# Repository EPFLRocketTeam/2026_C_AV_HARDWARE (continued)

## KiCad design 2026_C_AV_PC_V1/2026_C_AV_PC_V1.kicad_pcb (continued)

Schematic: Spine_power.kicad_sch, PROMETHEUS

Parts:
C5: 1u; C_0603_1608Metric
C6: 4u7; C_0603_1608Metric
C7: 1000p; C_0603_1608Metric
C8, C9, C11, C28, C29, C30, C50: 0u1; C_0603_1608Metric
C10: 100n; C_0603_1608Metric
C33, C34: 10u; C_0603_1608Metric
D9, D29, D53, D54, D55: PESD5V0S1UL; D_SOD-882; Mouser PESD5V0S1UL-QYL
D11, D12, D25, D36: LED; LED_0603_1608Metric
D57, D58, D61, D62, D63, D64: PESD3V3S1UL; D_SOD-882; Mouser 771-PESD3V3L1UL315
F1: Polyfuse; D_0805_2012Metric
F2: Polyfuse; Fuse_2920_7451Metric
H1, H2, H3, H4: MountingHole_Pad; MountingHole_2.2mm_M2_Pad
IC1: INA228AIDGSR; INA228; Mouser Part Number 595-INA228AIDGSR
IC4: MCP1642D-50I_MS; MCP1642; Mouser Part Number 579-MCP1642D-50I/MS
IC9: TPS25221DRVR; SON65P200X200X80-7N; Mouser Part Number 595-TPS25221DRVR
J7, J19: USB_B_Mini; USB_Mini-B_Lumberg_2486_01_Horizontal
J8: 24Vin; AMASS_XT60-M; PARTREV V1.2
J9: SPINE_in; STEWART_SS-12800-009; PARTREV A0; DigiKey_Part_Number 380-SS-12800-009-ND
J10: microSD_holder; Mouser Part Number 798-DM3ATSFPEJM541
J15: SPINE_out; STEWART_SS-12800-009; PARTREV A0; DigiKey_Part_Number 380-SS-12800-009-ND
J22: 24Vout; AMASS_XT60-M; PARTREV V1.2
JP3, JP4: SolderJumper_2_Open; SolderJumper-2_P1.3mm_Open_RoundedPad1.0x1.5mm
L1: 4u7; WE-TPC_282892; Mouser Part Number 710-744025004
R13: 100k; R_0603_1608Metric
R14: 13m; R_0805_2012Metric
R15: 120; R_0603_1608Metric
R16, R17, R35, R45: 1k1; R_0603_1608Metric
R32: 4K7; R_0603_1608Metric
R33: 32k; R_0603_1608Metric
R34, R60: 10k; R_0603_1608Metric
R58, R59: 54k9; R_0603_1608Metric
TP5: +24V; TestPoint_THTPad_D1.5mm_Drill0.7mm
TP6: CANH; TestPoint_THTPad_D1.5mm_Drill0.7mm
TP7: CANL; TestPoint_THTPad_D1.5mm_Drill0.7mm
TP8: +5V; TestPoint_THTPad_D1.5mm_Drill0.7mm
TP9: +3V3; TestPoint_THTPad_D1.5mm_Drill0.7mm
TP11: 5V_IN_SPINE; TestPoint_THTPad_D1.5mm_Drill0.7mm
TP13: 5V_IN_USB; TestPoint_THTPad_D1.5mm_Drill0.7mm
TP16: +5V_IN; TestPoint_THTPad_D1.5mm_Drill0.7mm
U5: MCP1727-3302xSN; SOIC-8_3.9x4.9mm_P1.27mm
U6: MCP2542FDxMF; SOIC-8_3.9x4.9mm_P1.27mm
U10: TPS2116DRL; SOT-583-8
U12, U13: USBLC6-2P6; SOT-666

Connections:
+3V3: C5.1, C8.2, C10.2, C11.2, D12.2 (A), IC1.1 (A1), IC1.2 (A0), IC1.6 (VS), J10.4 (VDD), R13.1, TP9.1, U5.7 (Sense), U5.8 (Vout), U6.5 (VIO); also elsewhere on the board
+5V: C9.1, C34.2, D11.2 (A), IC4.4 (VOUT), TP8.1, U6.3 (VDD); also elsewhere on the board
+24V: D36.2 (A), IC1.9 (IN-), R14.2, TP5.1; also elsewhere on the board
/Project Architecture/STM32/FDCAN_RX: U6.4 (RXD); also elsewhere on the board
/Project Architecture/STM32/FDCAN_TX: U6.1 (TXD); also elsewhere on the board
/Project Architecture/STM32/PWRGD: R13.2, U5.5 (PWRGD); also elsewhere on the board
/Project Architecture/STM32/SCL: IC1.4 (SDA); also elsewhere on the board
/Project Architecture/STM32/SDA: IC1.5 (SCL); also elsewhere on the board
/Project Architecture/STM32/SD_CLK: D64.1 (K), J10.5 (CLK); also elsewhere on the board
/Project Architecture/STM32/SD_CMD: D63.1 (K), J10.3 (CMD); also elsewhere on the board
/Project Architecture/STM32/SD_DAT0: D58.1 (K), J10.7 (DAT0); also elsewhere on the board
/Project Architecture/STM32/SD_DAT1: D61.1 (K), J10.8 (DAT1); also elsewhere on the board
/Project Architecture/STM32/SD_DAT2: D57.1 (K), J10.1 (DAT2); also elsewhere on the board
/Project Architecture/STM32/SD_DAT3: D62.1 (K), J10.2 (CD/DAT3); also elsewhere on the board
/Project Architecture/STM32/USB2_D+: U13.1 (I/O1); also elsewhere on the board
/Project Architecture/STM32/USB2_D-: U13.3 (I/O2); also elsewhere on the board
/Project Architecture/STM32/USB_D+: U12.1 (I/O1); also elsewhere on the board
/Project Architecture/STM32/USB_D-: U12.3 (I/O2); also elsewhere on the board
/Project Architecture/Spine&power/3V3_K: D12.1 (K), R17.1
/Project Architecture/Spine&power/5V_K: D11.1 (K), R16.1
/Project Architecture/Spine&power/24V_K: D36.1 (K), R45.1
/Project Architecture/Spine&power/24V_c: F2.1, J8.P (POS), J22.P (POS)
/Project Architecture/Spine&power/+5V_IN: C6.1, C30.2, C33.1, IC4.8 (VIN), JP3.1 (A), L1.1, R32.1, TP16.1, U5.1 (Vin), U5.2 (Vin), U5.3 (~SHDN), U10.2 (VOUT), U10.7 (VOUT)
/Project Architecture/Spine&power/+5V_SPINE: C28.2, D9.1 (K), J9.4, J15.4, R33.1, TP11.1, U10.3 (VIN1), U10.5 (MODE)
/Project Architecture/Spine&power/+5V_USB: C50.2, IC9.4 (EN), IC9.6 (IN), J7.1 (VBUS), R59.1, TP13.1, U12.5 (VBUS)
/Project Architecture/Spine&power/+5V_USB_p: F1.1, IC9.1 (OUT)
/Project Architecture/Spine&power/CANH: D29.1 (K), D54.1 (K), J9.2, J15.2, R15.1, TP6.1, U6.7 (CANH)
/Project Architecture/Spine&power/CANL: D53.1 (K), D55.1 (K), J9.3, J15.3, R15.2, TP7.1, U6.6 (CANL)
/Project Architecture/Spine&power/D2+: J19.3 (D+), U13.6 (I/O1)
/Project Architecture/Spine&power/D2-: J19.2 (D-), U13.4 (I/O2)
/Project Architecture/Spine&power/D+: J7.3 (D+), U12.6 (I/O1)
/Project Architecture/Spine&power/D-: J7.2 (D-), U12.4 (I/O2)
/Project Architecture/Spine&power/Delay: C7.1, U5.6 (Cdelay)
/Project Architecture/Spine&power/EN: IC4.1 (EN), JP3.2 (B), JP4.2 (B)
/Project Architecture/Spine&power/PR1: R33.2, R34.1, U10.4 (PR1)
/Project Architecture/Spine&power/ST: D25.2 (A), JP4.1 (A), R32.2, R60.1, U10.8 (ST)
/Project Architecture/Spine&power/ST_K: D25.1 (K), R35.1
/Project Architecture/Spine&power/SW: IC4.5 (SW), L1.2
/Project Architecture/Spine&power/VIN2: C29.2, F1.2, U10.6 (VIN2)
/Project Architecture/Spine&power/Vin+: F2.2, IC1.8 (VBUS), IC1.10 (IN+), R14.1
GND: C5.2, C6.2, C7.2, C8.1, C9.2, C10.1, C11.1, C28.1, C29.1, C30.1, C33.2, C34.1, C50.1, D9.2 (A), D29.2 (A), D53.2 (A), D54.2 (A), D55.2 (A), D57.2 (A), D58.2 (A), D61.2 (A), D62.2 (A), D63.2 (A), D64.2 (A), H1.1, H2.1, H3.1, H4.1, IC1.7 (GND), IC4.6 (PGND), IC4.7 (SGND), IC9.5 (GND), IC9.7 (EP), J7.5 (GND), J7.6 (Shield), J8.N (NEG), J9.1, J9.SH1 (SHIELD), J9.SH2 (SHIELD), J10.6 (VSS), J10.MP1, J10.MP2, J10.MP3, J10.MP4, J10.MP5, J10.MP6, J10.MP7, J15.1, J15.SH1 (SHIELD), J15.SH2 (SHIELD), J19.5 (GND), J19.6 (Shield), J22.N (NEG), R16.2, R17.2, R34.2, R35.2, R45.2, R58.2, R60.2, U5.4 (GND), U6.2 (VSS), U6.8 (STBY), U6.9 (VSS), U10.1 (GND), U12.2 (GND), U13.2 (GND); also elsewhere on the board
unnamed: IC9.2 (ILIM), R58.1
unnamed: IC9.3 (~FAULT), R59.2

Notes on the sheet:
SPINE & POWER
I2C Address: 0x45
Status LED + Debug
5V Boost
Power MUX
Tension sensor
+3V3 LDO
CAN FD Transceiver
SPINE connector
Over Current Protection USB
DESIGN NOTES: Internal ESD protection +13kV
MicroSD holder
ST from the power mux desable the boost when USB is connected to prevent back current
USB for data + power
Battery power

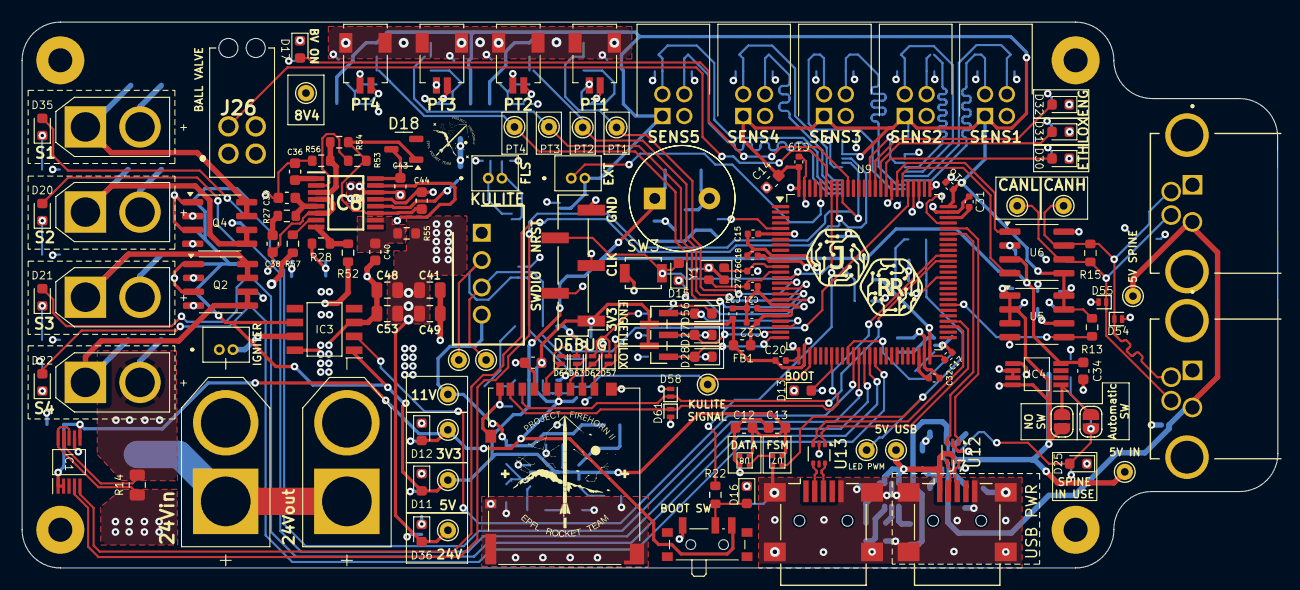
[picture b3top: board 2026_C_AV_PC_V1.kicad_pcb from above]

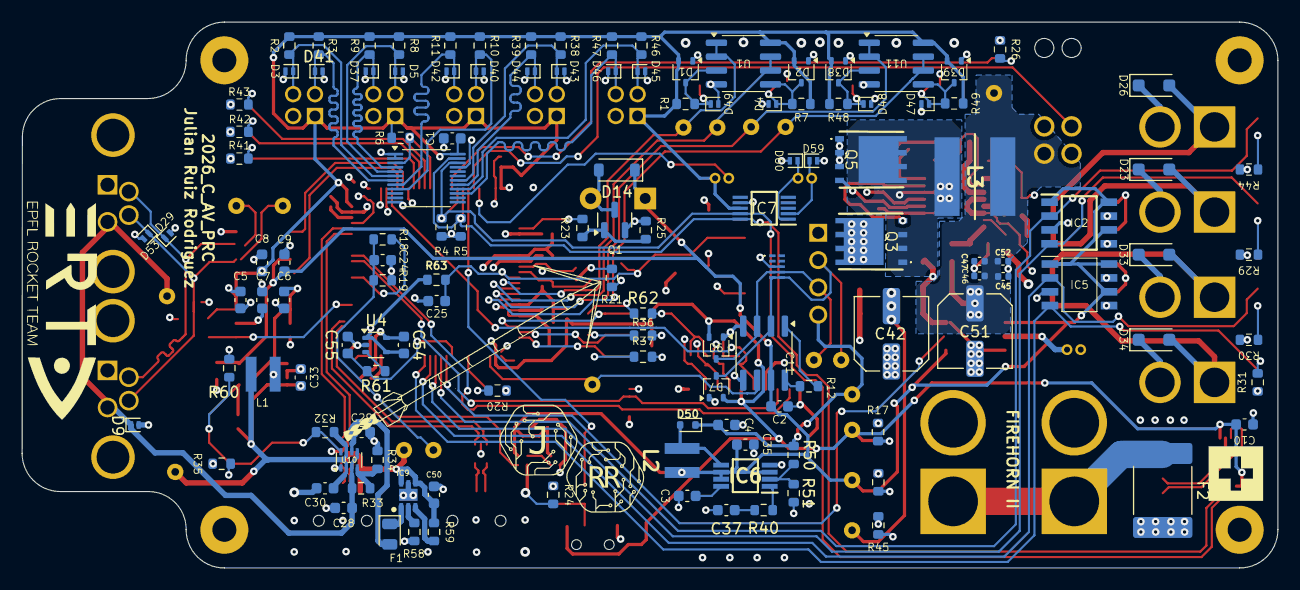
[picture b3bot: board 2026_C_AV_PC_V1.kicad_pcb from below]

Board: 4 copper layers, 115.0 x 50.0 mm, 265 parts (129 on the bottom side), 145 nets.

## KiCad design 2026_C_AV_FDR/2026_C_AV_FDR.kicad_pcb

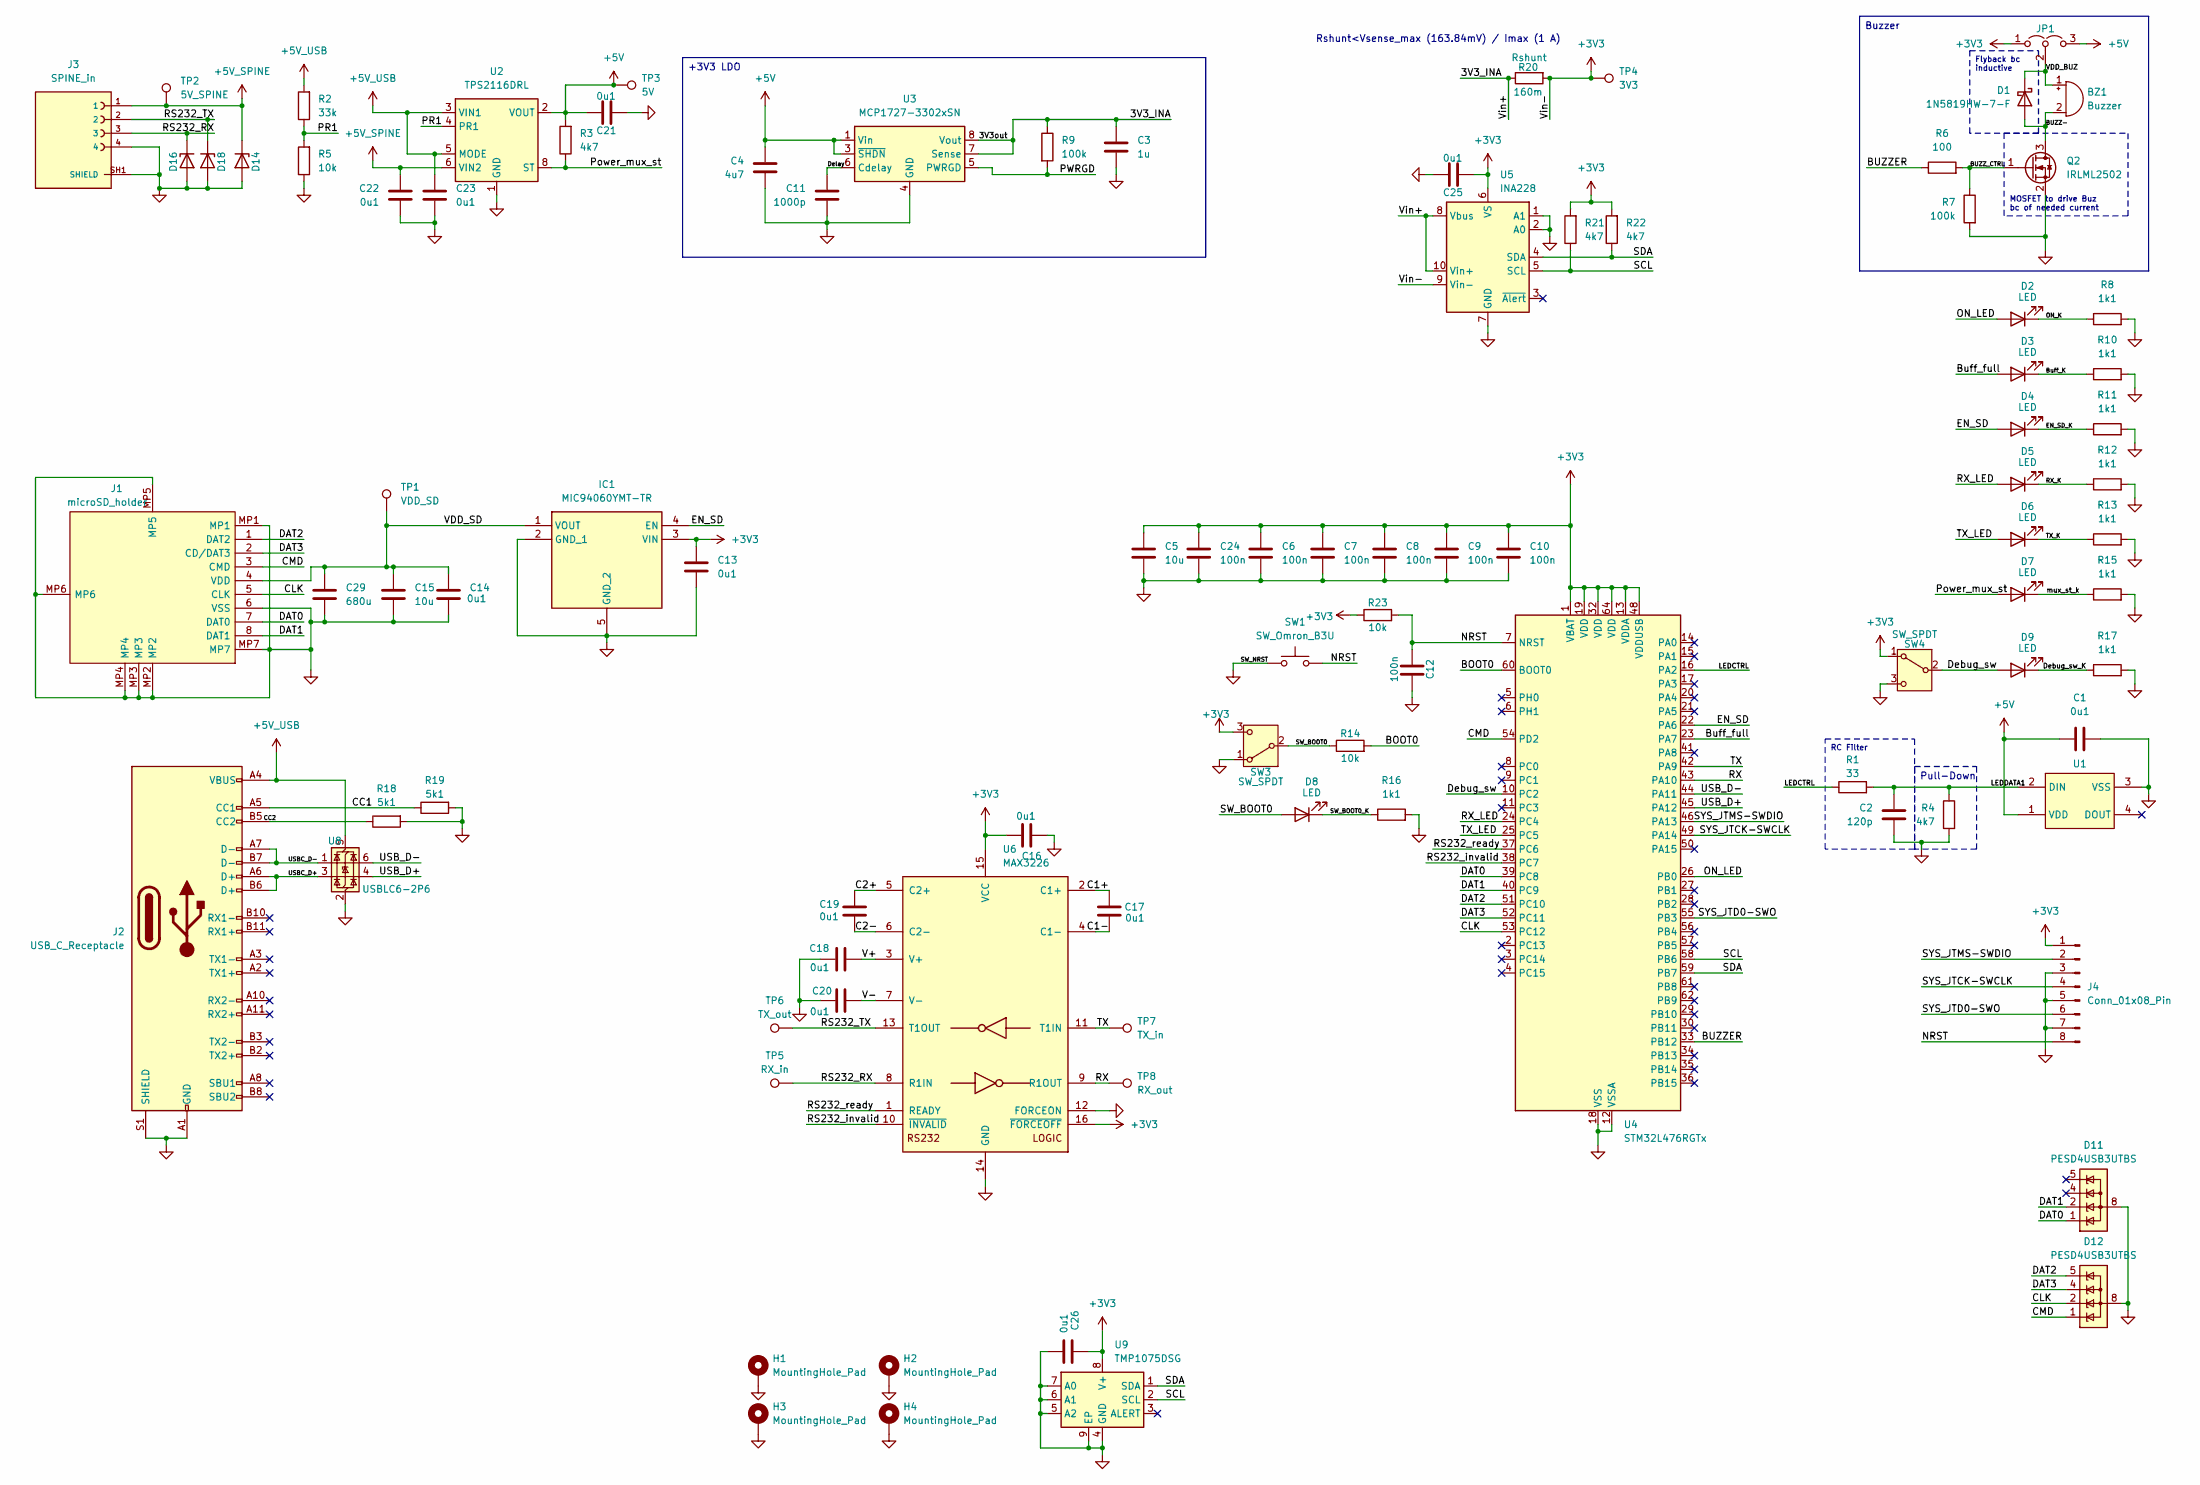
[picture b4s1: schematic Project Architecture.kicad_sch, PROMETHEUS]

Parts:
BZ1: Buzzer
C1, C13, C14, C16, C17, C18, C19, C20, C21, C22, C23, C25, C26: 0u1; C_0603_1608Metric
C2: 120p; C_0603_1608Metric
C3: 1u; C_0603_1608Metric
C4: 4u7; C_0603_1608Metric
C5, C15: 10u; C_0603_1608Metric
C6, C7, C8, C9, C10, C24: 100n; C_0402_1005Metric
C11: 1000p; C_0603_1608Metric
C12: 100n; C_0603_1608Metric
C29: 680u; C_Elec_6.3x7.7; Mouser No 667-EEE-FTJ681XAP
D1: 1N5819HW-7-F; D_SOD-123
D2, D3, D4, D5, D6, D7, D8, D9: LED; LED_0603_1608Metric
D11, D12: PESD4USB3UTBS; PESD4USB3UTBSQX
D14, D16, D18: TPD1E05U06DYAR; D_SOD-323_HandSoldering
H1, H2, H3, H4: MountingHole_Pad; MountingHole_2.2mm_M2_Pad
IC1: MIC94060YMT-TR; SON50P160X120X60-5N-D; Mouser Part Number 998-MIC94060YMTTR
J1: microSD_holder; Mouser Part Number 798-DM3ATSFPEJM541
J2: USB_C_Receptacle; USB_C_Receptacle_Molex_105450-0101
J3: SPINE_in; STEWART_SS-12800-009; PARTREV A0; DigiKey_Part_Number 380-SS-12800-009-ND
J4: Conn_01x08_Pin; PinHeader_2x04_P2.54mm_Vertical
JP1: Jumper_3_Open; SolderJumper-3_P1.3mm_Open_RoundedPad1.0x1.5mm
Q2: IRLML2502; SOT-23
R1: 33; R_0603_1608Metric
R2: 33k; R_0603_1608Metric
R3, R4, R21, R22: 4k7; R_0603_1608Metric
R5, R14, R23: 10k; R_0603_1608Metric
R6: 100; R_0603_1608Metric
R7, R9: 100k; R_0603_1608Metric
R8, R10, R11, R12, R13, R15, R16, R17: 1k1; R_0603_1608Metric
R18, R19: 5k1; R_0603_1608Metric
R20: 160m; R_0805_2012Metric
SW1: SW_Omron_B3U; SW_SPST_B3U-1000P
SW3, SW4: SW_SPDT; SW_SPDT_PCM12
TP1: VDD_SD; TestPoint_Pad_D2.0mm
TP2: 5V_SPINE; TestPoint_THTPad_D2.0mm_Drill1.0mm
TP3: 5V; TestPoint_THTPad_D2.0mm_Drill1.0mm
TP4: 3V3; TestPoint_THTPad_D2.0mm_Drill1.0mm
TP5: RX_in; TestPoint_THTPad_D2.0mm_Drill1.0mm
TP6: TX_out; TestPoint_THTPad_D2.0mm_Drill1.0mm
TP7: TX_in; TestPoint_THTPad_D2.0mm_Drill1.0mm
TP8: RX_out; TestPoint_THTPad_D2.0mm_Drill1.0mm
U1: RGBLED_1; NEW_RGB_LED
U2: TPS2116DRL; SOT-583-8
U3: MCP1727-3302xSN; SOIC-8_3.9x4.9mm_P1.27mm
U4: STM32L476RGTx; LQFP-64_10x10mm_P0.5mm
U5: INA228; VSSOP-10_3x3mm_P0.5mm
U6: MAX3226; SSOP-16_5.3x6.2mm_P0.65mm
U8: USBLC6-2P6; SOT-666
U9: TMP1075DSG; WSON-8-1EP_2x2mm_P0.5mm_EP0.9x1.6mm

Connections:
+3V3: C5.1, C6.1, C7.1, C8.1, C9.1, C10.1, C13.1, C16.2, C24.1, C25.1, C26.1, IC1.3 (VIN), J4.1, JP1.1 (A), R20.2, R21.2, R22.2, R23.1, SW3.3 (C), SW4.1 (A), TP4.1, U4.1 (VBAT), U4.13 (VDDA), U4.19 (VDD), U4.32 (VDD), U4.48 (VDDUSB), U4.64 (VDD), U5.6 (VS), U5.9 (Vin-), U6.15 (VCC), U6.16 (~FORCEOFF), U9.8 (V+)
+5V: C1.1, C4.1, C21.2, JP1.3 (B), R3.2, TP3.1, U1.1 (VDD), U2.2 (VOUT), U2.7 (VOUT), U3.1 (Vin), U3.2 (Vin), U3.3 (~SHDN)
+5V_SPINE: C22.1, D14.1 (K), J3.1, TP2.1, U2.6 (VIN2)
+5V_USB: C23.1, J2.A4 (VBUS), J2.A9 (VBUS), J2.B4 (VBUS), J2.B9 (VBUS), R2.2, U2.3 (VIN1), U2.5 (MODE), U8.5 (VBUS)
/Project Architecture/3V3_INA: C3.1, R9.1, R20.1, U3.7 (Sense), U3.8 (Vout), U5.8 (Vbus), U5.10 (Vin+)
/Project Architecture/BOOT0: R14.2, U4.60 (BOOT0)
/Project Architecture/BUZZ-: BZ1.2 (-), D1.2 (A), Q2.3 (D)
/Project Architecture/BUZZER: R6.1, U4.33 (PB12)
/Project Architecture/BUZZ_CTRL: Q2.1 (G), R6.2, R7.1
/Project Architecture/Buff_K: D3.1 (K), R10.1
/Project Architecture/Buff_full: D3.2 (A), U4.23 (PA7)
/Project Architecture/C1+: C17.1, U6.2 (C1+)
/Project Architecture/C1-: C17.2, U6.4 (C1-)
/Project Architecture/C2+: C19.1, U6.5 (C2+)
/Project Architecture/C2-: C19.2, U6.6 (C2-)
/Project Architecture/CC1: J2.A5 (CC1), R19.1
/Project Architecture/CC2: J2.B5 (CC2), R18.1
/Project Architecture/CLK: D12.2, D12.9, J1.5 (CLK), U4.53 (PC12)
/Project Architecture/CMD: D12.1, D12.10, J1.3 (CMD), U4.54 (PD2)
/Project Architecture/DAT0: D11.1, D11.10, J1.7 (DAT0), U4.39 (PC8)
/Project Architecture/DAT1: D11.2, D11.9, J1.8 (DAT1), U4.40 (PC9)
/Project Architecture/DAT2: D12.5, D12.6, J1.1 (DAT2), U4.51 (PC10)
/Project Architecture/DAT3: D12.4, D12.7, J1.2 (CD/DAT3), U4.52 (PC11)
/Project Architecture/Debug_sw: D9.2 (A), SW4.2 (B), U4.10 (PC2)
/Project Architecture/Debug_sw_K: D9.1 (K), R17.1
/Project Architecture/Delay: C11.1, U3.6 (Cdelay)
/Project Architecture/EN_SD: D4.2 (A), IC1.4 (EN), U4.22 (PA6)
/Project Architecture/EN_SD_K: D4.1 (K), R11.1
/Project Architecture/LEDCTRL: R1.1, U4.16 (PA2)
/Project Architecture/LEDDATA1: C2.2, R1.2, R4.1, U1.2 (DIN)
/Project Architecture/NRST: C12.1, J4.8, R23.2, SW1.2, U4.7 (NRST)
/Project Architecture/ON_K: D2.1 (K), R8.1
/Project Architecture/ON_LED: D2.2 (A), U4.26 (PB0)
/Project Architecture/PR1: R2.1, R5.2, U2.4 (PR1)
/Project Architecture/PWRGD: R9.2, U3.5 (PWRGD)
/Project Architecture/Power_mux_st: D7.2 (A), R3.1, U2.8 (ST)
/Project Architecture/RS232_RX: D16.1 (K), J3.3, TP5.1, U6.8 (R1IN)
/Project Architecture/RS232_TX: D18.1 (K), J3.2, TP6.1, U6.13 (T1OUT)
/Project Architecture/RS232_invalid: U4.38 (PC7), U6.10 (~INVALID)
/Project Architecture/RS232_ready: U4.37 (PC6), U6.1 (READY)
/Project Architecture/RX: TP8.1, U4.43 (PA10), U6.9 (R1OUT)
/Project Architecture/RX_K: D5.1 (K), R12.1
/Project Architecture/RX_LED: D5.2 (A), U4.24 (PC4)
/Project Architecture/SCL: R21.1, U4.58 (PB6), U5.5 (SCL), U9.2 (SCL)
/Project Architecture/SDA: R22.1, U4.59 (PB7), U5.4 (SDA), U9.1 (SDA)
/Project Architecture/SW_BOOT0: D8.2 (A), R14.1, SW3.2 (B)
/Project Architecture/SW_BOOT0_K: D8.1 (K), R16.1
/Project Architecture/SYS_JTCK-SWCLK: J4.4, U4.49 (PA14)
/Project Architecture/SYS_JTD0-SWO: J4.6, U4.55 (PB3)
/Project Architecture/SYS_JTMS-SWDIO: J4.2, U4.46 (PA13)
/Project Architecture/TX: TP7.1, U4.42 (PA9), U6.11 (T1IN)
/Project Architecture/TX_K: D6.1 (K), R13.1
/Project Architecture/TX_LED: D6.2 (A), U4.25 (PC5)
/Project Architecture/USBC_D+: J2.A6 (D+), J2.B6 (D+), U8.3 (I/O2)
/Project Architecture/USBC_D-: J2.A7 (D-), J2.B7 (D-), U8.1 (I/O1)
/Project Architecture/USB_D+: U4.45 (PA12), U8.4 (I/O2)
/Project Architecture/USB_D-: U4.44 (PA11), U8.6 (I/O1)
/Project Architecture/V+: C18.2, U6.3 (V+)
/Project Architecture/V-: C20.2, U6.7 (V-)
/Project Architecture/VDD_BUZ: BZ1.1 (+), D1.1 (K), JP1.2 (C)
/Project Architecture/VDD_SD: C14.1, C15.1, C29.1, IC1.1 (VOUT), J1.4 (VDD), TP1.1
/Project Architecture/mux_st_k: D7.1 (K), R15.1
GND: C1.2, C2.1, C3.2, C4.2, C5.2, C6.2, C7.2, C8.2, C9.2, C10.2, C11.2, C12.2, C13.2, C14.2, C15.2, C16.1, C18.1, C20.1, C21.1, C22.2, C23.2, C24.2, C25.2, C26.2, C29.2, D11.3, D11.8, D12.3, D12.8, D14.2 (A), D16.2 (A), D18.2 (A), H1.1, H2.1, H3.1, H4.1, IC1.2 (GND_1), IC1.5 (GND_2), J1.6 (VSS), J1.MP1, J1.MP2, J1.MP3, J1.MP4, J1.MP5, J1.MP6, J1.MP7, J2.A1 (GND), J2.A12 (GND), J2.B1 (GND), J2.B12 (GND), J2.S1 (SHIELD), J3.4, J3.SH1 (SHIELD), J3.SH2 (SHIELD), J4.3, J4.5, J4.7, Q2.2 (S), R4.2, R5.1, R7.2, R8.2, R10.2, R11.2, R12.2, R13.2, R15.2, R16.2, R17.2, R18.2, R19.2, SW1.1, SW3.1 (A), SW4.3 (C), U1.3 (VSS), U2.1 (GND), U3.4 (GND), U4.12 (VSSA), U4.18 (VSS), U4.31 (VSS), U4.47 (VSS), U4.63 (VSS), U5.1 (A1), U5.2 (A0), U5.7 (GND), U6.12 (FORCEON), U6.14 (GND), U8.2 (GND), U9.4 (GND), U9.5 (A2), U9.6 (A1), U9.7 (A0), U9.9 (EP)

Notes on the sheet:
Rshunt<Vsense_max (163.84mV) / Imax (1 A)
Flyback bc inductive
MOSFET to drive Buz bc of needed current
Pull-Down
Buzzer
RC Filter
+3V3 LDO

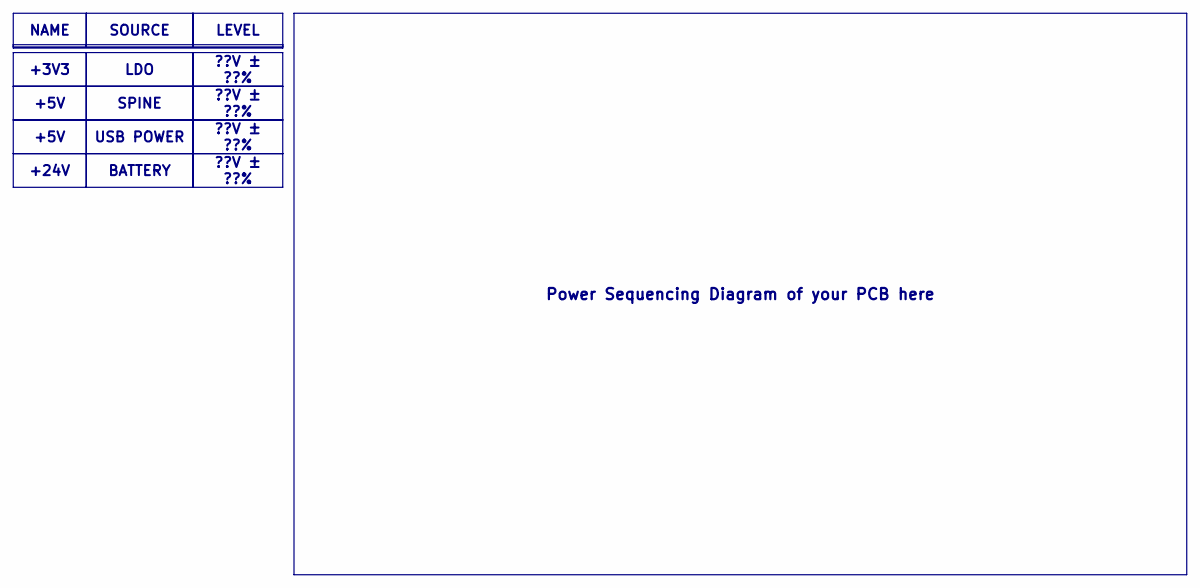
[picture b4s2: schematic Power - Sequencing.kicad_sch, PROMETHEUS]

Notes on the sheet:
+5V
??V ± ??%
SOURCE
BATTERY
SPINE
+24V
USB POWER
LDO
Power Sequencing Diagram of your PCB here
LEVEL
+3V3
NAME

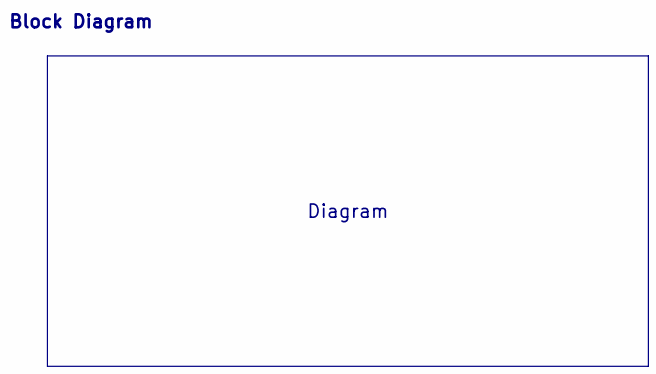
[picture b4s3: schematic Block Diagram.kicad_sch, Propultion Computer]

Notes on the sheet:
Block Diagram
Diagram

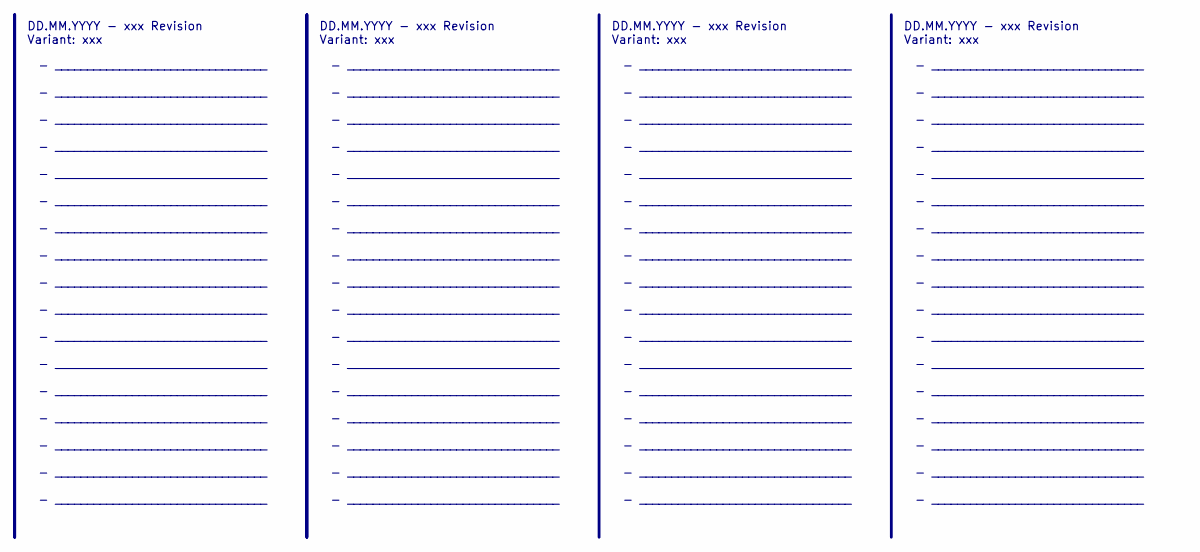
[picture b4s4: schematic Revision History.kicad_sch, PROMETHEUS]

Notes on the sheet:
- _________________________________ - _________________________________ - _________________________________ - _________________________________ - _________________________________ - _________________________________ - _________________________________ - _________________________________ - _________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
DD.MM.YYYY - xxx Revision Variant: xxx

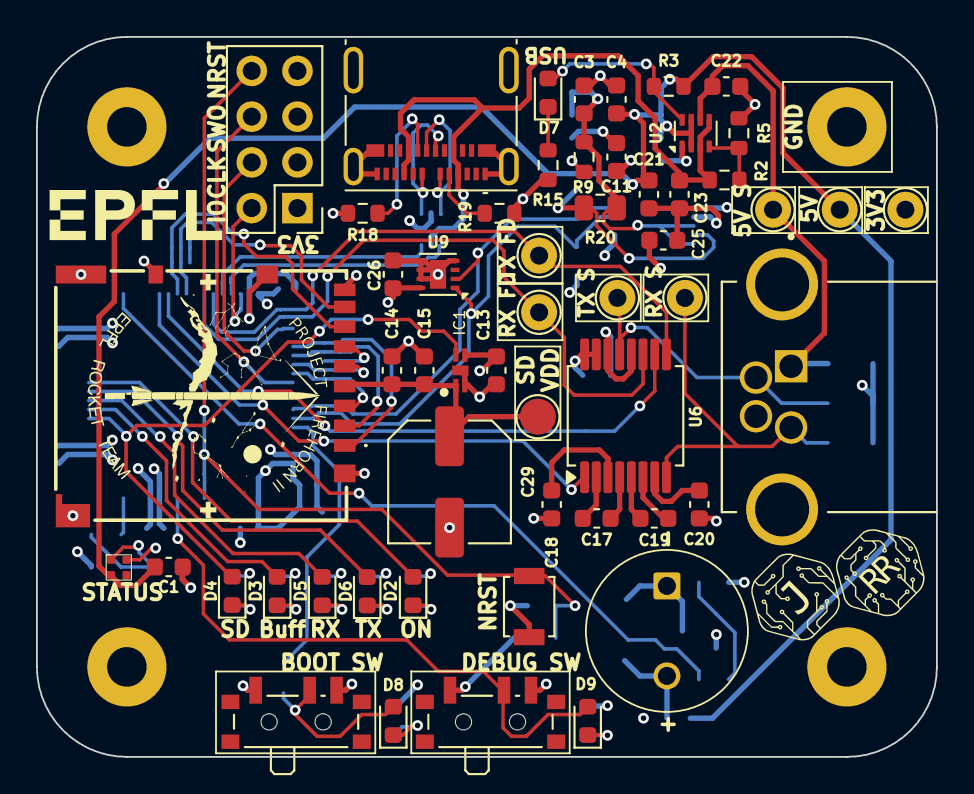
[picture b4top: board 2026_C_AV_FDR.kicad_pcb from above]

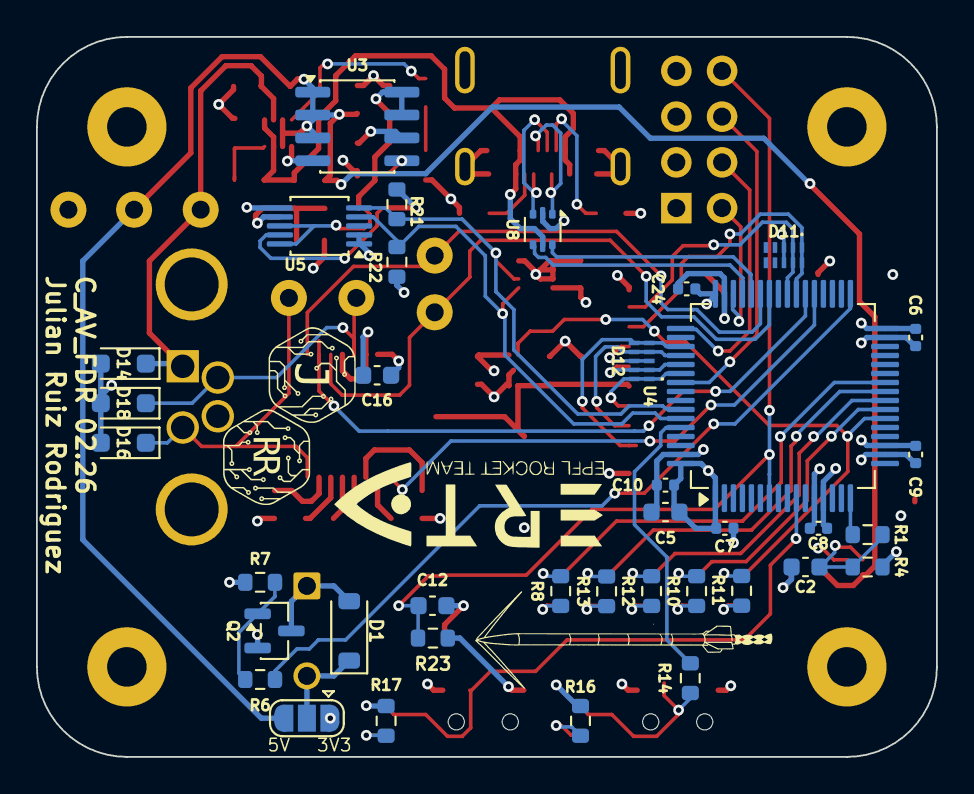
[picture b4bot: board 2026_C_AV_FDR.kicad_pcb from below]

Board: 4 copper layers, 50.0 x 40.0 mm, 95 parts (37 on the bottom side), 63 nets.

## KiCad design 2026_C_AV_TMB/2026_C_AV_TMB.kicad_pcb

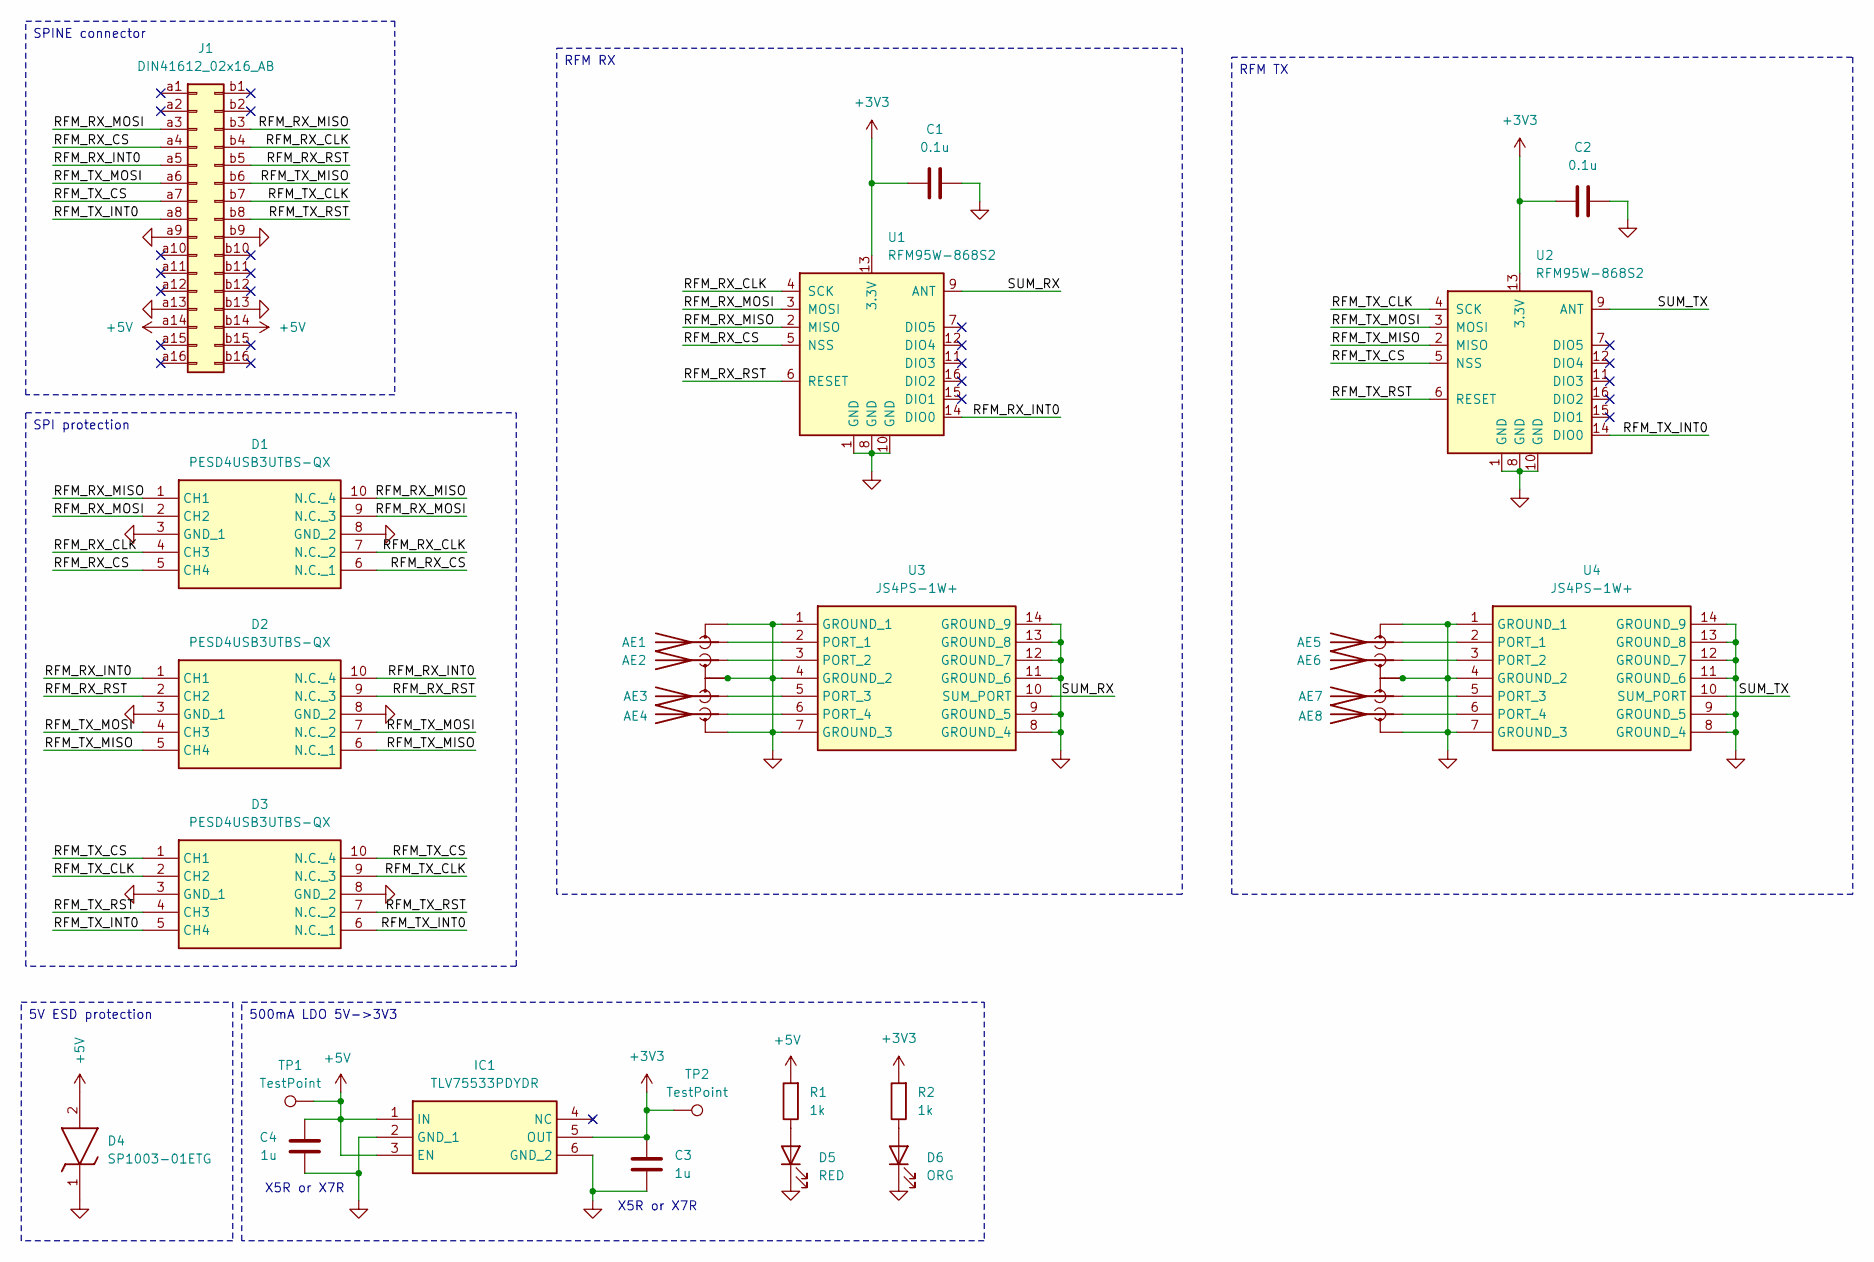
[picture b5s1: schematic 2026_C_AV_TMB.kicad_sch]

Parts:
AE1, AE2, AE3, AE4, AE5, AE6, AE7, AE8: Antenna_Shield; 9011436RFX
C1, C2: 0.1u; C_0603_1608Metric
C3, C4: 1u; C_0603_1608Metric
D1, D2, D3: PESD4USB3UTBS-QX; PESD4USB3UTBSQX; Manufacturer_Part_Number PESD4USB3UTBS-QX
D4: SP1003-01ETG; SP100301ETG; Mouser Part Number 576-SP1003-01ETG
D5: RED; LED_0603_1608Metric
D6: ORG; LED_0603_1608Metric
IC1: TLV75533PDYDR; Mouser Part Number 595-TLV75533PDYDR
J1: DIN41612_02x16_AB; DIN41612_B2_2x16_Male_Horizontal_THT
R1, R2: 1k; R_0603_1608Metric
TP1, TP2: TestPoint; TestPoint_THTPad_D1.5mm_Drill0.7mm
U1, U2: RFM95W-868S2; HOPERF_RFM9XW_SMD
U3, U4: JS4PS-1W+; JS4PS1W; Mouser Part Number 139-JS4PS-1W

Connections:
+3V3: C1.1, C2.1, C3.1, IC1.5 (OUT), R2.2, TP2.1, U1.13 (3.3V), U2.13 (3.3V)
+5V: C4.1, D4.2 (A), IC1.1 (IN), IC1.3 (EN), J1.a14, J1.b14, R1.2, TP1.1
/RFM_RX_CLK: D1.4 (CH3), D1.7 (N.C._2), J1.b4, U1.4 (SCK)
/RFM_RX_CS: D1.5 (CH4), D1.6 (N.C._1), J1.a4, U1.5 (NSS)
/RFM_RX_INT0: D2.1 (CH1), D2.10 (N.C._4), J1.a5, U1.14 (DIO0)
/RFM_RX_MISO: D1.1 (CH1), D1.10 (N.C._4), J1.b3, U1.2 (MISO)
/RFM_RX_MOSI: D1.2 (CH2), D1.9 (N.C._3), J1.a3, U1.3 (MOSI)
/RFM_RX_RST: D2.2 (CH2), D2.9 (N.C._3), J1.b5, U1.6 (RESET)
/RFM_TX_CLK: D3.2 (CH2), D3.9 (N.C._3), J1.b7, U2.4 (SCK)
/RFM_TX_CS: D3.1 (CH1), D3.10 (N.C._4), J1.a7, U2.5 (NSS)
/RFM_TX_INT0: D3.5 (CH4), D3.6 (N.C._1), J1.a8, U2.14 (DIO0)
/RFM_TX_MISO: D2.5 (CH4), D2.6 (N.C._1), J1.b6, U2.2 (MISO)
/RFM_TX_MOSI: D2.4 (CH3), D2.7 (N.C._2), J1.a6, U2.3 (MOSI)
/RFM_TX_RST: D3.4 (CH3), D3.7 (N.C._2), J1.b8, U2.6 (RESET)
/SUM_RX: U1.9 (ANT), U3.10 (SUM_PORT)
/SUM_TX: U2.9 (ANT), U4.10 (SUM_PORT)
GND: AE1.2 (Shield), AE1.3, AE1.4, AE1.5, AE2.2 (Shield), AE2.3, AE2.4, AE2.5, AE3.2 (Shield), AE3.3, AE3.4, AE3.5, AE4.2 (Shield), AE4.3, AE4.4, AE4.5, AE5.2 (Shield), AE5.3, AE5.4, AE5.5, AE6.2 (Shield), AE6.3, AE6.4, AE6.5, AE7.2 (Shield), AE7.3, AE7.4, AE7.5, AE8.2 (Shield), AE8.3, AE8.4, AE8.5, C1.2, C2.2, C3.2, C4.2, D1.3 (GND_1), D1.8 (GND_2), D2.3 (GND_1), D2.8 (GND_2), D3.3 (GND_1), D3.8 (GND_2), D4.1 (K), D5.1 (K), D6.1 (K), IC1.2 (GND_1), IC1.6 (GND_2), J1.a9, J1.a13, J1.b9, J1.b13, U1.1 (GND), U1.8 (GND), U1.10 (GND), U2.1 (GND), U2.8 (GND), U2.10 (GND), U3.1 (GROUND_1), U3.4 (GROUND_2), U3.7 (GROUND_3), U3.8 (GROUND_4), U3.9 (GROUND_5), U3.11 (GROUND_6), U3.12 (GROUND_7), U3.13 (GROUND_8), U3.14 (GROUND_9), U4.1 (GROUND_1), U4.4 (GROUND_2), U4.7 (GROUND_3), U4.8 (GROUND_4), U4.9 (GROUND_5), U4.11 (GROUND_6), U4.12 (GROUND_7), U4.13 (GROUND_8), U4.14 (GROUND_9)
unnamed: AE1.1 (A), U3.2 (PORT_1)
unnamed: AE2.1 (A), U3.3 (PORT_2)
unnamed: AE3.1 (A), U3.5 (PORT_3)
unnamed: AE4.1 (A), U3.6 (PORT_4)
unnamed: AE5.1 (A), U4.2 (PORT_1)
unnamed: AE6.1 (A), U4.3 (PORT_2)
unnamed: AE7.1 (A), U4.5 (PORT_3)
unnamed: AE8.1 (A), U4.6 (PORT_4)
unnamed: D5.2 (A), R1.1
unnamed: D6.2 (A), R2.1

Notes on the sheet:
X5R or X7R
SPI protection
5V ESD protection
RFM RX
500mA LDO 5V->3V3
SPINE connector
RFM TX

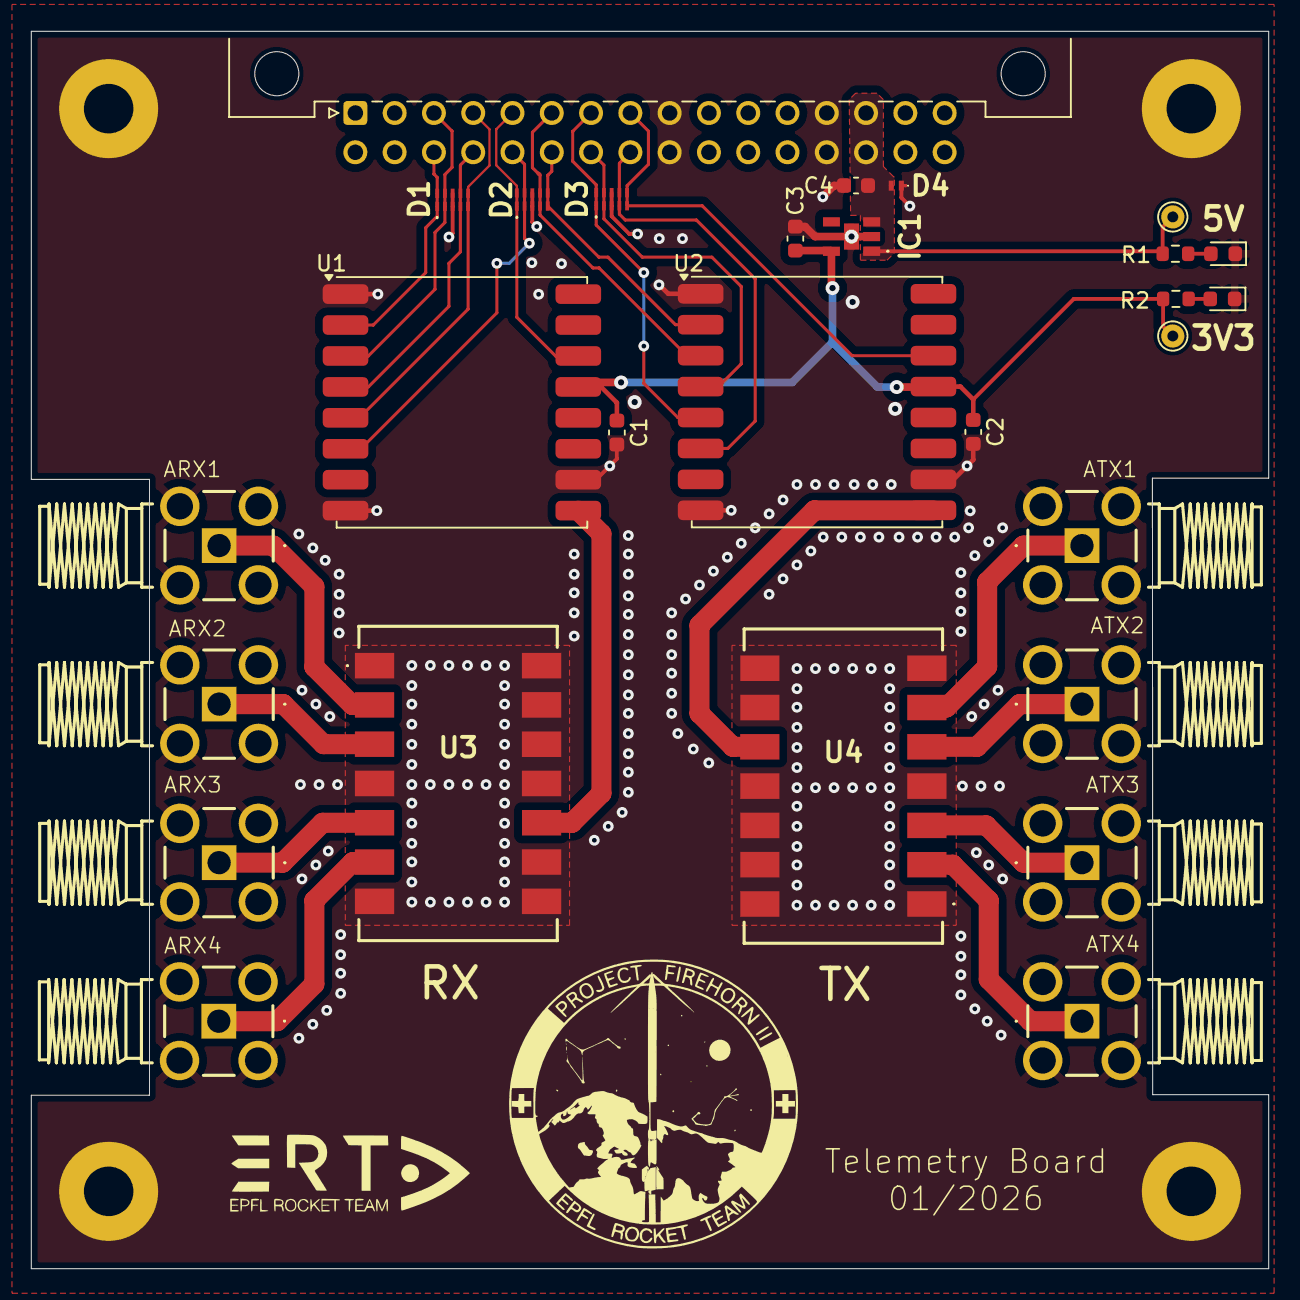
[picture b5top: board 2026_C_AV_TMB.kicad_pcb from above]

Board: 2 copper layers, 80.0 x 80.0 mm, 28 parts (0 on the bottom side), 27 nets.

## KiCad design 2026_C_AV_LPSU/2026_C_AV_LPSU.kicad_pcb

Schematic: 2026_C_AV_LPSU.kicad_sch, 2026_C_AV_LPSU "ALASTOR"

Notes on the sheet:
DESIGN NOTES: Example text for informational design notes.
DESIGN NOTES: Example text for critical design notes.
DESIGN NOTES: Example text for cautionary design notes.
DEBUG NOTES: Example text for debug notes.
LAYOUT NOTES: Example text for critical layout guidelines.

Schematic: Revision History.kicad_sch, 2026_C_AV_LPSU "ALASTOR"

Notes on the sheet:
- _________________________________ - _________________________________ - _________________________________ - _________________________________ - _________________________________ - _________________________________ - _________________________________ - _________________________________ - _________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
DD.MM.YYYY - xxx Revision Variant: xxx

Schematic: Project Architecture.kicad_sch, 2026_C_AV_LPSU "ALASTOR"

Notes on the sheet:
Project Architecture

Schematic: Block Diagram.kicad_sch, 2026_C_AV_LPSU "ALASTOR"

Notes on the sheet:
Block Diagram

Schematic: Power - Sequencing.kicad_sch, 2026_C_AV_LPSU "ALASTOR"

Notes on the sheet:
+??V
??V ± ??%
SOURCE
SOURCE NAME
Power Sequencing Diagram
LEVEL
NAME
